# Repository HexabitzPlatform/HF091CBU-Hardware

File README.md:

# HF091CBU-Hardware
Hexabitz STM32F091CBU6 DevKit Hardware Design

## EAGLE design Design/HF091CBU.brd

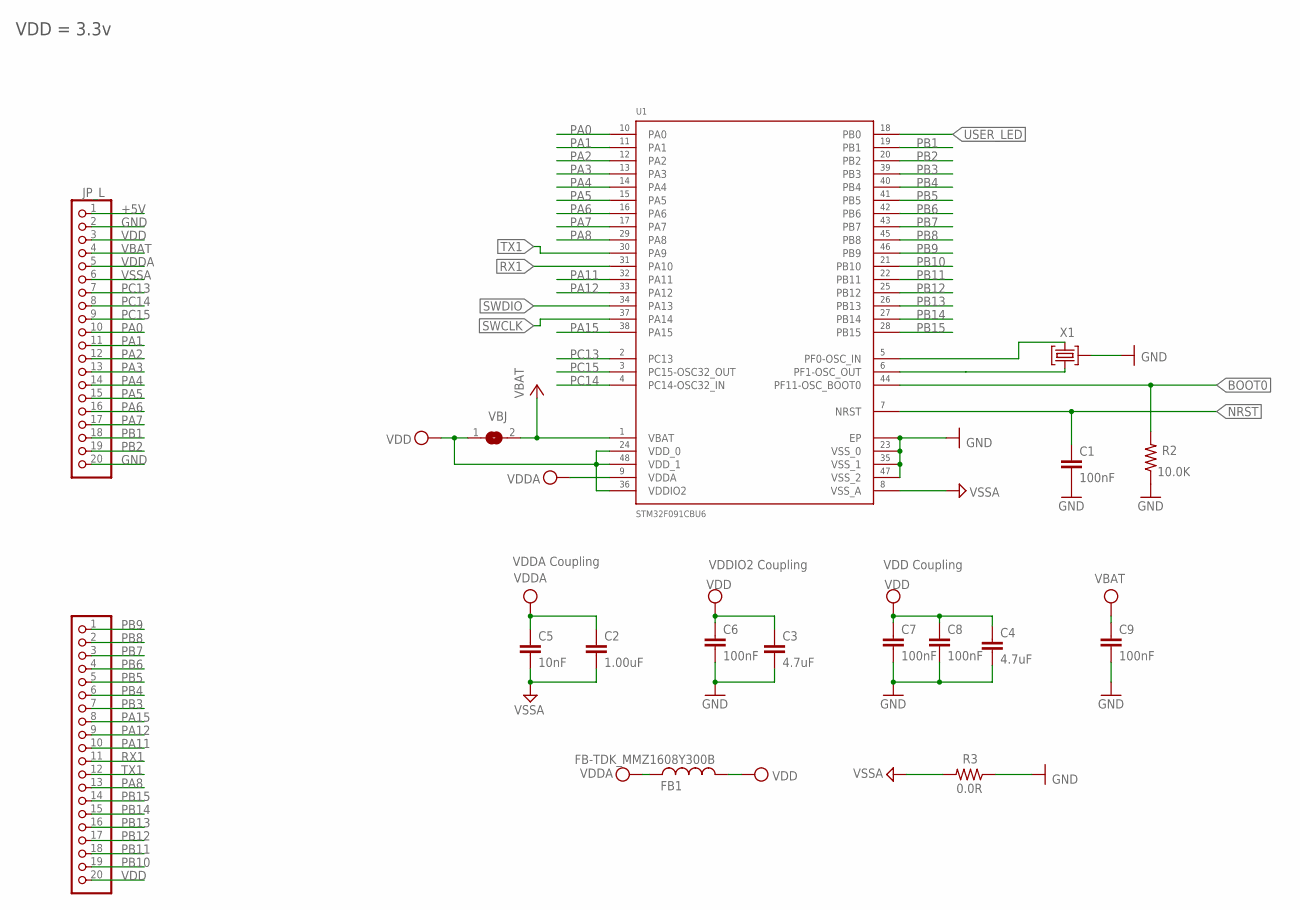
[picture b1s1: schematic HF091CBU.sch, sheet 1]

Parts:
C1, C6, C8: 100nF; C-0603; TOLERANCE 10%; VOLTAGE_RATING 10V; MPN C0603C104K8RACTU
C2: 1.00uF; C-0805
C3, C4: 4.7uF; C-0805
C5: 10nF; C-0603; TOLERANCE 10%; VOLTAGE_RATING 50V; MPN C0603C103K5RACTU
C7: 100nF; C-0603; TOLERANCE 10%; VOLTAGE_RATING 10; MPN C0603C104K8RACTU
C9: 100nF; C-0603; TOLERANCE 10V; VOLTAGE_RATING 10%; MPN C0603C104K8RACTU
FB1: FB-TDK_MMZ1608Y300B; FB-0603; MPN MMZ1608Y300B
JP_L: PINHD-1X20; 1X20
JP_R: PINHD-1X20; 1X20
R2: 10.0K; R-0603; TOLERANCE 5%; MPN CRCW060310K0JNEB
R3: 0.0R; R-0603; MPN RC0603JR-070RL
U1: STM32F091CBU6
VBJ: SJ
X1: XTALL_CSTCE8M00G52

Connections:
+5V: JP_L.1; also elsewhere on the board
BOOT0: R2.2, U1.P$44 (PF11-OSC_BOOT0); also elsewhere on the board
GND: C1.2, C3.2, C4.2, C6.2, C7.2, C8.2, C9.2, JP_L.2, JP_L.20, R2.1, R3.1, U1.EP, U1.P$23 (VSS_0), U1.P$35 (VSS_1), U1.P$47 (VSS_2), X1.P$2 (2); also elsewhere on the board
unnamed: U1.P$5 (PF0-OSC_IN), X1.P$1 (1)
unnamed: U1.P$6 (PF1-OSC_OUT), X1.P$3 (3)
NRST: C1.1, U1.P$7 (NRST); also elsewhere on the board
PA0: JP_L.10, U1.P$10 (PA0)
PA1: JP_L.11, U1.P$11 (PA1)
PA2: JP_L.12, U1.P$12 (PA2)
PA3: JP_L.13, U1.P$13 (PA3)
PA4: JP_L.14, U1.P$14 (PA4)
PA5: JP_L.15, U1.P$15 (PA5)
PA6: JP_L.16, U1.P$16 (PA6)
PA7: JP_L.17, U1.P$17 (PA7)
PA8: JP_R.13, U1.P$29 (PA8)
PA11: JP_R.10, U1.P$32 (PA11)
PA12: JP_R.9, U1.P$33 (PA12)
PA15: JP_R.8, U1.P$38 (PA15)
PB1: JP_L.18, U1.P$19 (PB1)
PB2: JP_L.19, U1.P$20 (PB2)
PB3: JP_R.7, U1.P$39 (PB3)
PB4: JP_R.6, U1.P$40 (PB4)
PB5: JP_R.5, U1.P$41 (PB5)
PB6: JP_R.4, U1.P$42 (PB6)
PB7: JP_R.3, U1.P$43 (PB7)
PB8: JP_R.2, U1.P$45 (PB8)
PB9: JP_R.1, U1.P$46 (PB9)
PB10: JP_R.19, U1.P$21 (PB10)
PB11: JP_R.18, U1.P$22 (PB11)
PB12: JP_R.17, U1.P$25 (PB12)
PB13: JP_R.16, U1.P$26 (PB13)
PB14: JP_R.15, U1.P$27 (PB14)
PB15: JP_R.14, U1.P$28 (PB15)
PC13: JP_L.7, U1.P$2 (PC13)
PC14: JP_L.8, U1.P$3 (PC14-OSC32_IN)
PC15: JP_L.9, U1.P$4 (PC15-OSC32_OUT)
RX1: JP_R.11, U1.P$31 (PA10); also elsewhere on the board
SWCLK: U1.P$37 (PA14); also elsewhere on the board
SWDIO: U1.P$34 (PA13); also elsewhere on the board
TX1: JP_R.12, U1.P$30 (PA9); also elsewhere on the board
USER_LED: U1.P$18 (PB0); also elsewhere on the board
VBAT: C9.1, JP_L.4, U1.P$1 (VBAT), VBJ.2
VDD: C3.1, C4.1, C6.1, C7.1, C8.1, FB1.2, JP_L.3, JP_R.20, U1.P$24 (VDD_0), U1.P$36 (VDDIO2), U1.P$48 (VDD_1), VBJ.1; also elsewhere on the board
VDDA: C2.1, C5.1, FB1.1, JP_L.5, U1.P$9 (VDDA)
VSSA: C2.2, C5.2, JP_L.6, R3.2, U1.P$8 (VSS_A)

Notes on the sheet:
VDDA Coupling
VDDIO2 Coupling
VDD Coupling
VDD = 3.3v

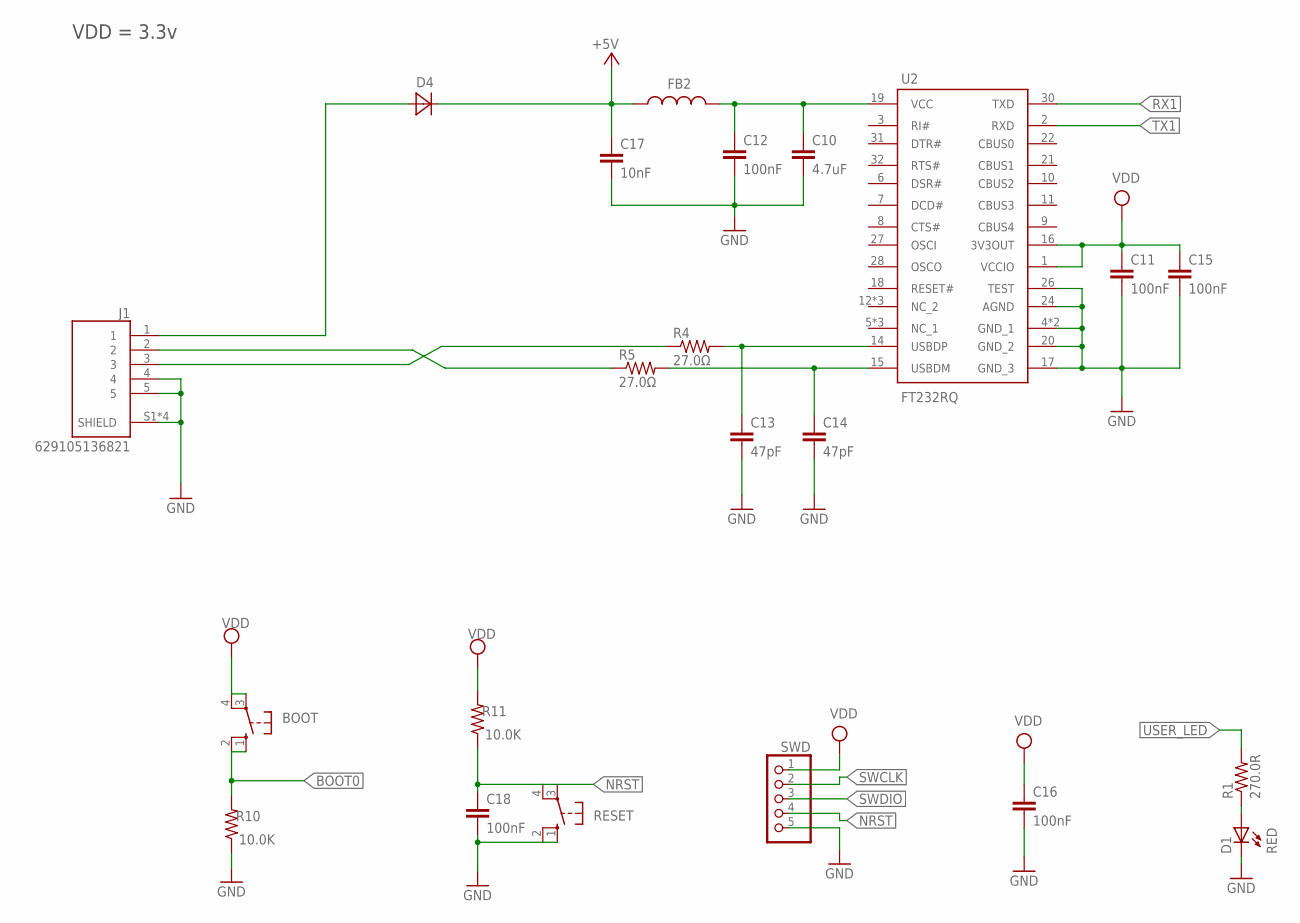
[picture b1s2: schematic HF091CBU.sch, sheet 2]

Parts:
BOOT: 10-XX; B3F-10XX
C10: 4.7uF; C-0805
C11, C12, C15: 100nF; C-0603; TOLERANCE ±10%; VOLTAGE_RATING 16.0 V; MPN 0603YC104K4T2A
C13, C14: 47pF; C-0603; TOLERANCE ±5%; VOLTAGE_RATING 50.0 V; MPN 06035A470JAT2A
C16, C18: 100nF; C-0603; TOLERANCE 10%; VOLTAGE_RATING 10V; MPN C0603C104K8RACTU
C17: 10nF; C-0603; TOLERANCE ±10%; VOLTAGE_RATING 16.0 V; MPN 0603YC104K4T2A
D1: RED; VLMS1300-GS08; MPN VLMS1300-GS08
D4: DIOD-SOD-123; SOD123
FB2: FB-TDK_MMZ1608Y300B; FB-0603; MPN MMZ1608Y300B
J1: 629105136821; WE_629105136821
R1: 270.0R; R-0603; TOLERANCE 1%; MPN RC0603FR-07270RL
R4, R5: 27.0Ω; R-0603; TOLERANCE ±1%; MPN CRCW060327R0FKEA
R10, R11: 10.0K; R-0603; TOLERANCE 5%; MPN RC0603JR-0710KL
RESET: 10-XX; B3F-10XX
SWD: PINHD-1X5/90; 1X05/90
TRIMBLE-LOGO1: HEXABITZ-LOGO_NO_BOTTOM_SPLIT
U2: FT232RQ; QFN50P500X500X90-33N

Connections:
+5V: C17.1, D4.2 (C), FB2.1; also elsewhere on the board
BOOT0: BOOT.1 (S), BOOT.2 (S1), R10.2; also elsewhere on the board
GND: C10.2, C11.2, C12.2, C13.2, C14.2, C15.2, C16.2, C17.2, C18.2, D1.C, J1.4, J1.5, J1.S1 (SHIELD), J1.S2 (SHIELD), J1.S3 (SHIELD), J1.S4 (SHIELD), R10.1, RESET.1 (S), RESET.2 (S1), SWD.5, U2.4 (GND_1), U2.17 (GND_3), U2.20 (GND_2), U2.24 (AGND), U2.26 (TEST), U2.33 (GND_1); also elsewhere on the board
unnamed: D4.1 (A), J1.1
unnamed: C10.1, C12.1, FB2.2, U2.19 (VCC)
unnamed: D1.A, R1.1
NRST: C18.1, R11.1, RESET.3, RESET.4 (P1), SWD.4; also elsewhere on the board
RX1: U2.30 (TXD); also elsewhere on the board
SWCLK: SWD.2; also elsewhere on the board
SWDIO: SWD.3; also elsewhere on the board
TX1: U2.2 (RXD); also elsewhere on the board
USBD_N: C14.1, R5.2, U2.15 (USBDM)
USBD_P: C13.1, R4.2, U2.14 (USBDP)
USB_N: J1.2, R5.1
USB_P: J1.3, R4.1
USER_LED: R1.2; also elsewhere on the board
VDD: BOOT.3, BOOT.4 (P1), C11.1, C15.1, C16.1, R11.2, SWD.1, U2.1 (VCCIO), U2.16 (3V3OUT); also elsewhere on the board

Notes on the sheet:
VDD = 3.3v

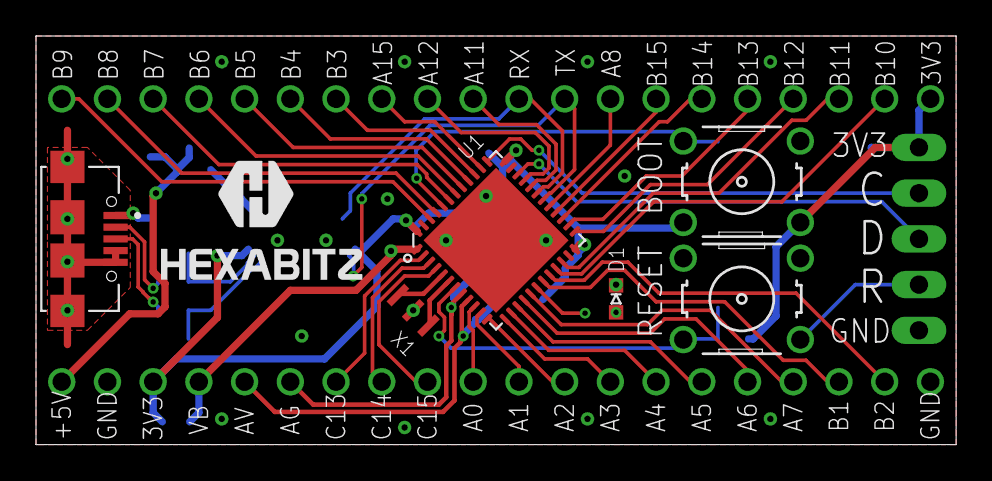
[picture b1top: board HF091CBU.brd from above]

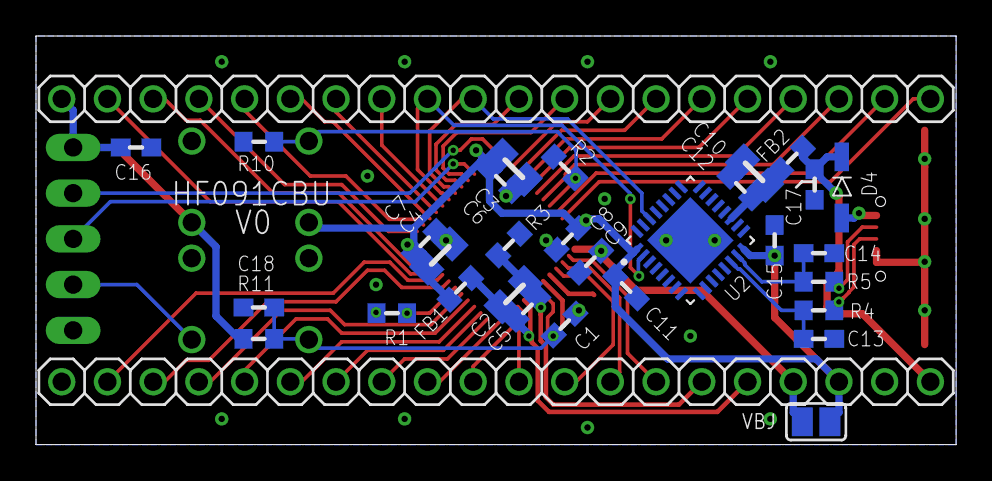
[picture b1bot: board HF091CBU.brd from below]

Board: 2 copper layers, 51.1 x 22.7 mm, 40 parts (30 on the bottom side), 52 nets.

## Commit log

2024-05-21 Make the tamplete Unchecked schematic
2024-07-15 All finish, reviewed version
2024-09-10 -Fixing an issue on the silkscreen layer
2024-09-14 Update the BOM but still need check
